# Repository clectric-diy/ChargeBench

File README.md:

# Charge
A collection of breakout boards and breadboard accessories to charge the Synth DIY projects on your workbench.

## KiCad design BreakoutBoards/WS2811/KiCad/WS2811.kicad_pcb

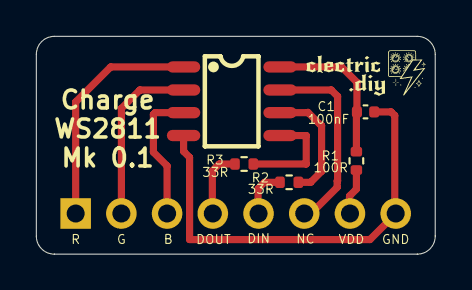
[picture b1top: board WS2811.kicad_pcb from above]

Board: 2 copper layers, 22.2 x 12.1 mm, 6 parts (1 on the bottom side), 8 nets.

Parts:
C1: 100nF; C_0402_1005Metric
J1: Conn_01x08_Pin; PinHeader_1x08_P2.54mm_Vertical
R1: 100R; R_0402_1005Metric
R2, R3: 33R; R_0402_1005Metric
U1: WS2811; SOP-8_L4.9-W3.9-P1.27-LS6.0-BL

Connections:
DIN: J1.5, R2.1, R2.2, U1.6 (DIN)
DOUT: J1.4, R3.1, R3.2, U1.5 (DO)
GND: C1.1, J1.8, U1.4 (GND)
NC: J1.6, U1.7 (NC)
OUTB: J1.3, U1.3 (OUTB)
OUTG: J1.2, U1.2 (OUTG)
OUTR: J1.1, U1.1 (OUTR)
VDD: C1.2, J1.7, R1.1, R1.2, U1.8 (VDD)

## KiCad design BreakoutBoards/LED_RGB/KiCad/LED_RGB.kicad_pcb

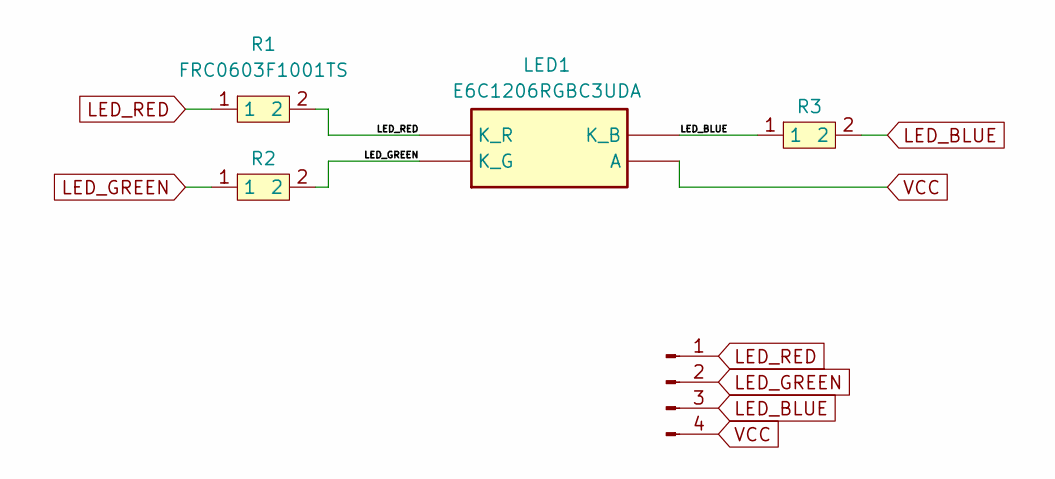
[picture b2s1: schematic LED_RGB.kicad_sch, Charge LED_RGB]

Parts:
J1: HDR-TH_4P-P2.54-V-M
LED1: E6C1206RGBC3UDA; Manufacturer_Part_Number E6C1206RGBC3UDA
R1, R2, R3: FRC0603F1001TS; R0603; LCSC Part C2907002

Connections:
LED_BLUE: J1.3, LED1.4 (K_B), R3.1, R3.2
LED_GREEN: J1.2, LED1.1 (K_G), R2.1, R2.2
LED_RED: J1.1, LED1.3 (K_R), R1.1, R1.2
VCC: J1.4, LED1.2 (A)

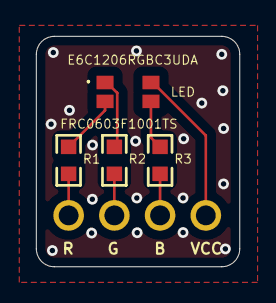
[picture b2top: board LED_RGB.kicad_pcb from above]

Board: 2 copper layers, 11.3 x 12.8 mm, 5 parts (1 on the bottom side), 4 nets.

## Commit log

2026-02-20 stubbed out READMEs for breakout boards
2026-02-20 replaced out of stock resistors
2026-02-20 reorganized under KiCad directory
2026-02-21 added via stitching
2026-02-21 added readme to led_rgb
2026-02-21 simplifing naming to "Charge"
2026-02-21 nesting in KiCad subdirectory
2026-02-22 created WS2811 breakout board

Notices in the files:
BreakoutBoards/LED_RGB/KiCad/LED_RGB.kicad_pcb:
Copyright © 2026 clectric.diy Licensed under CERN-OHL-W v2
